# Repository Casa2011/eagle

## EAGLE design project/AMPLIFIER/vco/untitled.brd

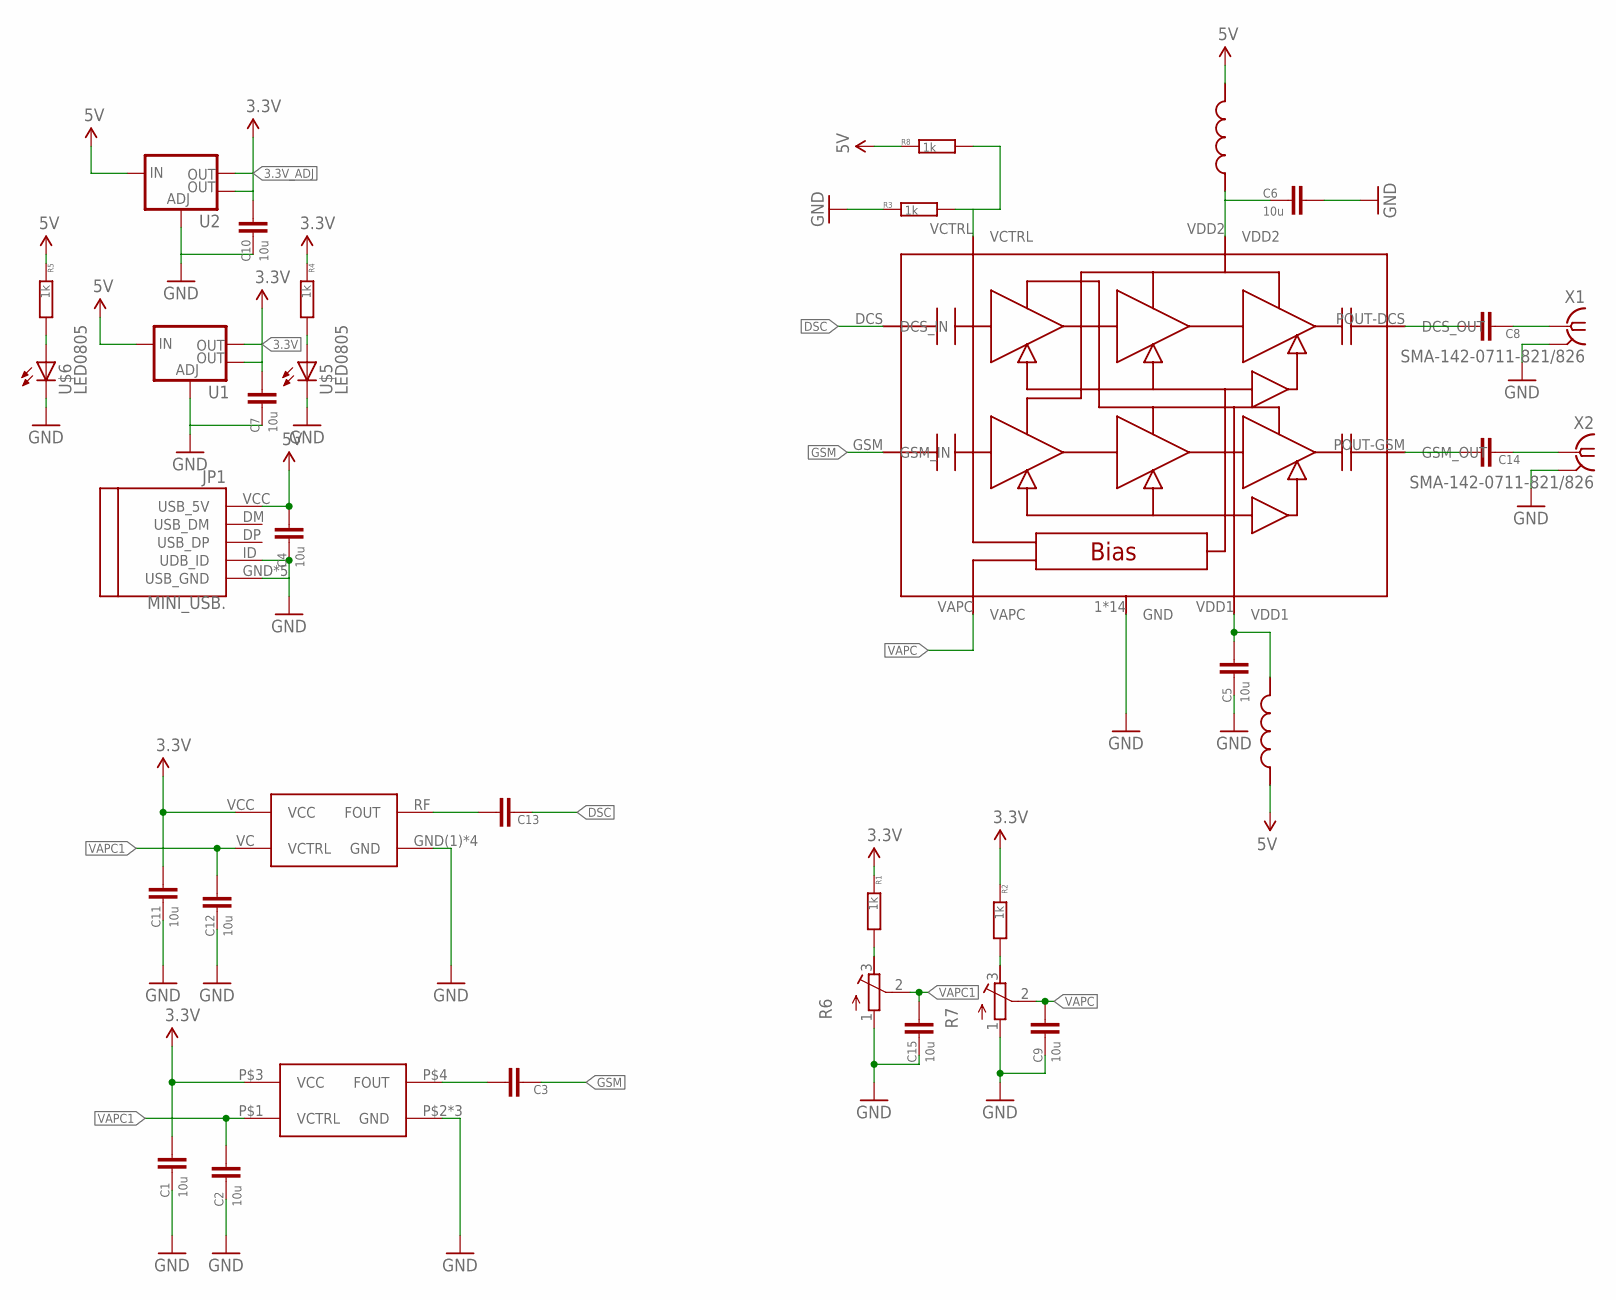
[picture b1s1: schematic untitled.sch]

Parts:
C1, C2, C4, C5, C6, C7, C9, C10, C11, C12, C15: 10u; C0805
C3, C8, C13, C14: CC0805; C0805
JP1: MINI_USB.; 32005-201
R1, R2, R3, R4, R5, R8: 1k; 0603
R6, R7: R-TRIMM64W; RTRIM64W
U1, U2: V_REG_LM1117SOT223; SOT223
U$1: FDK_IN089; FDK_IN_XX
U$2: RF-K-8A; RENESAS08123BA
U$3, U$4: L; L1
U$5, U$6: LED0805; 0805-LED
U$7: VCO_RX(1)
X1, X2: SMA-142-0711-821/826; J502-ND-142-0711-821/826

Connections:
3.3V: C1.1, C7.1, C11.1, R4.1, U1.2 (OUT), U1.4 (OUT), U$1.P$3 (VCC), U$7.VCC
3.3V_ADJ: C10.1, R1.1, R2.1, U2.2 (OUT), U2.4 (OUT)
5V: C4.1, JP1.VCC (USB_5V), R5.1, R8.1, U1.3 (IN), U2.3 (IN), U$3.2, U$4.1
DSC: C13.2, U$2.DCS (DCS_IN)
DSC->: C8.1, U$2.POUT-DCS (DCS_OUT)
GND: C1.2, C2.2, C4.2, C5.2, C6.1, C7.2, C9.2, C10.2, C11.2, C12.2, C15.2, JP1.GND (USB_GND), JP1.ID (UDB_ID), JP1.M1 (USB_GND), JP1.M2 (USB_GND), JP1.M3 (USB_GND), JP1.M4 (USB_GND), R3.1, R6.1 (A), R7.1 (A), U1.1 (ADJ), U2.1 (ADJ), U$1.P$2 (GND), U$1.P$5 (GND), U$1.P$6 (GND), U$2.1 (GND), U$2.2 (GND), U$2.3 (GND), U$2.4 (GND), U$2.5 (GND), U$2.6 (GND), U$2.7 (GND), U$2.8 (GND), U$2.9 (GND), U$2.10 (GND), U$2.11 (GND), U$2.12 (GND), U$2.13 (GND), U$2.14 (GND), U$5.C, U$6.C, U$7.GND(1) (GND), U$7.GND(2) (GND), U$7.GND(3) (GND), U$7.GND(4) (GND), X1.G@1 (2), X1.G@2 (2), X1.G@3 (2), X1.G@4 (2), X2.G@1 (2), X2.G@2 (2), X2.G@3 (2), X2.G@4 (2)
GSM: C3.2, U$2.GSM (GSM_IN)
unnamed: R1.2, R6.3 (E)
unnamed: R4.2, U$5.A
unnamed: R5.2, U$6.A
unnamed: R2.2, R7.3 (E)
unnamed: C3.1, U$1.P$4 (FOUT)
unnamed: C8.2, X1.1
unnamed: C6.2, U$2.VDD2, U$3.1
unnamed: C13.1, U$7.RF (FOUT)
unnamed: C14.2, X2.1
unnamed: C14.1, U$2.POUT-GSM (GSM_OUT)
unnamed: C5.1, U$2.VDD1, U$4.2
VAPC: C9.1, R7.2 (S), U$2.VAPC
VAPC1: C2.1, C12.1, C15.1, R6.2 (S), U$1.P$1 (VCTRL), U$7.VC (VCTRL)
VCTRL: R3.2, R8.2, U$2.VCTRL

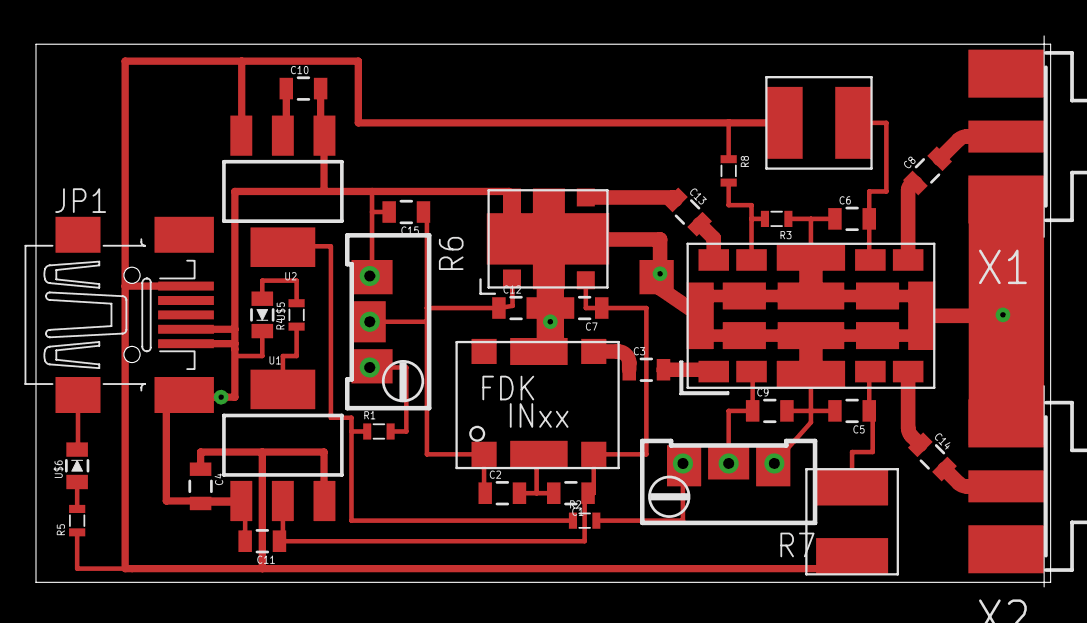
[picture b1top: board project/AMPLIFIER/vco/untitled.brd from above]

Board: 2 copper layers, 56.4 x 29.9 mm, 35 parts (0 on the bottom side), 21 nets.

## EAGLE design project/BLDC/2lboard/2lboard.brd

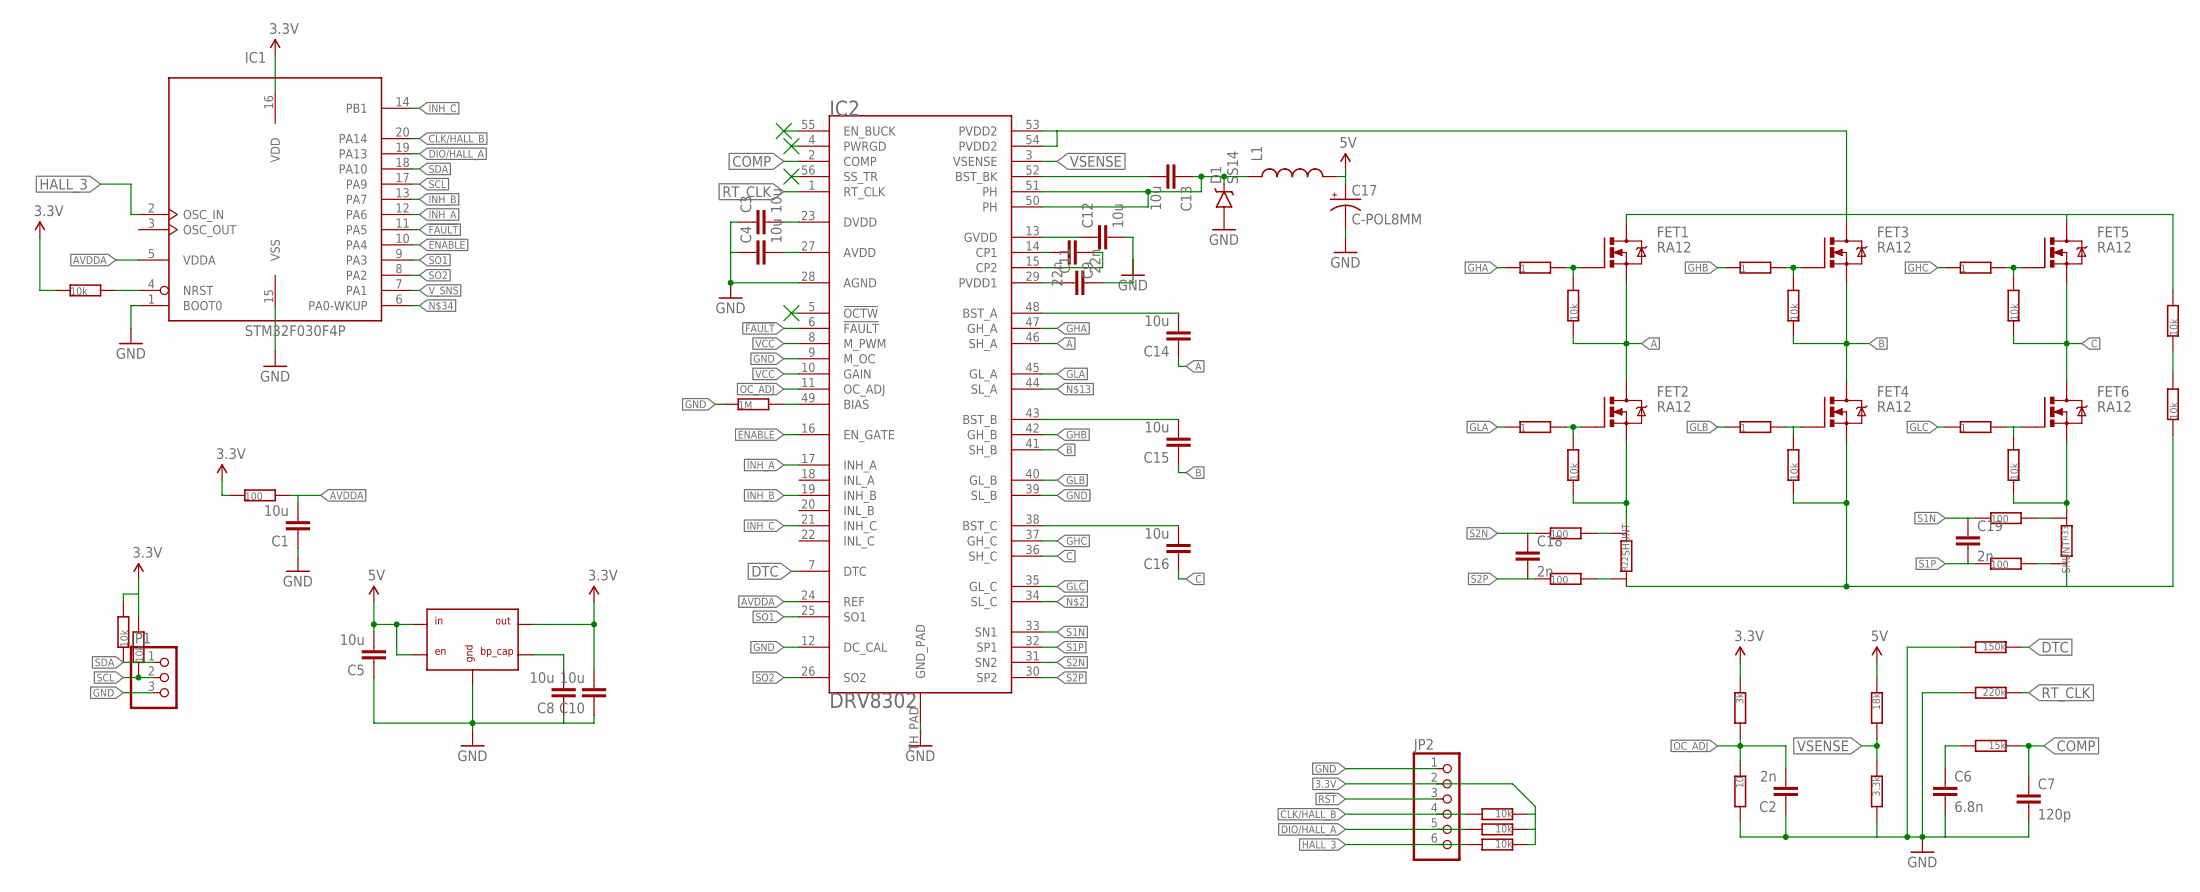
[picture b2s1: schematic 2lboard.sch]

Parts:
C1, C3, C4, C5, C8, C10, C12, C13, C14, C15, C16: 10u; C0805
C2, C18, C19: 2n; C0805
C6: 6.8n; C0805
C7: 120p; C0805
C9, C11: 22n; C0805
C17: C-POL8MM; PCAP8
D1: SS14; SMA-DIODE
FET1, FET2, FET3, FET4, FET5, FET6: RA12; POWERPAK_SO8
IC1: STM32F030F4P; TSSOP20-I
IC2: DRV8302; HTSSOP56DCA
IC3: LM258DG; SOT23-5L
JP1: PINHD-1X03_2.54; 1X03
JP2: PINHD-1X06_2.54; 1X06
L1: INDUCTORSRU1038; SRU1038
R1, R11, R12, R13, R14, R15, R20, R21, R25, R26, R31, R32, R34, R35: 10k; 0603
R2, R18, R19, R29, R30: 100; 0603
R3: 3k; 0603
R4: 10; 0603
R5: 1M; 0603
R6: 18k; 0603
R7: 3.3k; 0603
R8: 150k; 0603
R9: 220k; 0603
R10: 15k; 0603
R16, R17, R23, R24, R27, R28: 1; 0603
R22, R33: SHUNT

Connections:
3.3V: C10.2, IC1.16 (VDD), IC3.5 (OUT), JP2.2, R1.1, R2.1, R3.1, R11.2, R12.2, R13.1, R14.1, R15.1
5V: C5.2, C17.P$1 (+), IC3.1 (IN), IC3.3 (EN), L1.2, R6.1
!FAULT: IC1.11 (PA5), IC2.6 (!FAULT)
!RST: IC1.4 (NRST), JP2.3, R1.2
A: C14.1, FET1.1 (S), FET1.2 (S), FET1.3 (S), FET2.5 (D), FET2.6 (D), FET2.7 (D), FET2.8 (D), FET2.P$1 (D), IC2.46 (SH_A), R20.1
AVDDA: C1.2, IC1.5 (VDDA), IC2.24 (REF), R2.2
B: C15.1, FET3.1 (S), FET3.2 (S), FET3.3 (S), FET4.5 (D), FET4.6 (D), FET4.7 (D), FET4.8 (D), FET4.P$1 (D), IC2.41 (SH_B), R25.1
C: C16.1, FET5.1 (S), FET5.2 (S), FET5.3 (S), FET6.5 (D), FET6.6 (D), FET6.7 (D), FET6.8 (D), FET6.P$1 (D), IC2.36 (SH_C), R31.1
CLK/HALL_B: IC1.20 (PA14), JP2.4, R13.2
COMP: C7.1, IC2.2 (COMP), R10.1
DIO/HALL_A: IC1.19 (PA13), JP2.5, R14.2
DTC: IC2.7 (DTC), R8.1
ENABLE: IC1.10 (PA4), IC2.16 (EN_GATE)
GHA: IC2.47 (GH_A), R16.1
GHB: IC2.42 (GH_B), R23.1
GHC: IC2.37 (GH_C), R27.1
GLA: IC2.45 (GL_A), R17.1
GLB: IC2.40 (GL_B), R24.1
GLC: IC2.35 (GL_C), R28.1
GND: C1.1, C2.1, C3.1, C4.1, C5.1, C6.2, C7.2, C8.1, C10.1, C11.2, C12.2, C17.P$2 (-), D1.A, FET4.1 (S), FET4.2 (S), FET4.3 (S), IC1.1 (BOOT0), IC1.15 (VSS), IC2.9 (M_OC), IC2.12 (DC_CAL), IC2.28 (AGND), IC2.39 (SL_B), IC2.TH_PAD (GND_PAD), IC3.2 (GND), JP1.3, JP2.1, R4.2, R5.1, R7.2, R8.2, R9.2, R22.P$1 (1), R26.1, R33.P$2 (2), R35.1
HALL_3: IC1.2 (OSC_IN), JP2.6, R15.2
INH_A: IC1.12 (PA6), IC2.17 (INH_A)
INH_B: IC1.13 (PA7), IC2.19 (INH_B)
INH_C: IC1.14 (PB1), IC2.21 (INH_C)
unnamed: FET6.1 (S), FET6.2 (S), FET6.3 (S), IC2.34 (SL_C), R32.1, R33.P$1 (1)
unnamed: C14.2, IC2.48 (BST_A)
unnamed: C15.2, IC2.43 (BST_B)
unnamed: FET5.4 (G), R27.2, R31.2
unnamed: FET3.4 (G), R23.2, R25.2
unnamed: FET1.4 (G), R16.2, R20.2
unnamed: FET2.4 (G), R17.2, R21.2
unnamed: FET4.4 (G), R24.2, R26.2
unnamed: C16.2, IC2.38 (BST_C)
unnamed: FET6.4 (G), R28.2, R32.2
unnamed: IC2.49 (BIAS), R5.2
unnamed: FET2.1 (S), FET2.2 (S), FET2.3 (S), IC2.44 (SL_A), R21.1, R22.P$2 (2)
unnamed: C9.1, IC2.15 (CP2)
unnamed: C9.2, IC2.14 (CP1)
unnamed: C12.1, IC2.13 (GVDD)
unnamed: C13.2, IC2.52 (BST_BK)
unnamed: C13.1, D1.C, IC2.50 (PH), IC2.51 (PH), L1.1
unnamed: C6.1, R10.2
unnamed: C8.2, IC3.4 (CAP)
unnamed: C3.2, IC2.23 (DVDD)
unnamed: C4.2, IC2.27 (AVDD)
unnamed: C11.1, IC2.29 (PVDD1)
OC_ADJ: C2.2, IC2.11 (OC_ADJ), R3.2, R4.1
RT_CLK: IC2.1 (RT_CLK), R9.1
S1N: C19.1, IC2.33 (SN1), R29.1
S1P: C19.2, IC2.32 (SP1), R30.1
S2N: C18.1, IC2.31 (SN2), R18.1
S2P: C18.2, IC2.30 (SP2), R19.1
SCL: IC1.17 (PA9), JP1.2, R12.1
SDA: IC1.18 (PA10), JP1.1, R11.1
SO1: IC1.9 (PA3), IC2.25 (SO1)
SO2: IC1.8 (PA2), IC2.26 (SO2)
SS1N: R18.2, R22.P$4
SS1P: R19.2, R22.P$3
SS2N: R29.2, R33.P$3
SS2P: R30.2, R33.P$4
VCC: FET1.5 (D), FET1.6 (D), FET1.7 (D), FET1.8 (D), FET1.P$1 (D), FET3.5 (D), FET3.6 (D), FET3.7 (D), FET3.8 (D), FET3.P$1 (D), FET5.5 (D), FET5.6 (D), FET5.7 (D), FET5.8 (D), FET5.P$1 (D), IC2.8 (M_PWM), IC2.10 (GAIN), IC2.53 (PVDD2), IC2.54 (PVDD2), R34.2
VSENSE: IC2.3 (VSENSE), R6.2, R7.1
V_SNS: IC1.7 (PA1), R34.1, R35.2

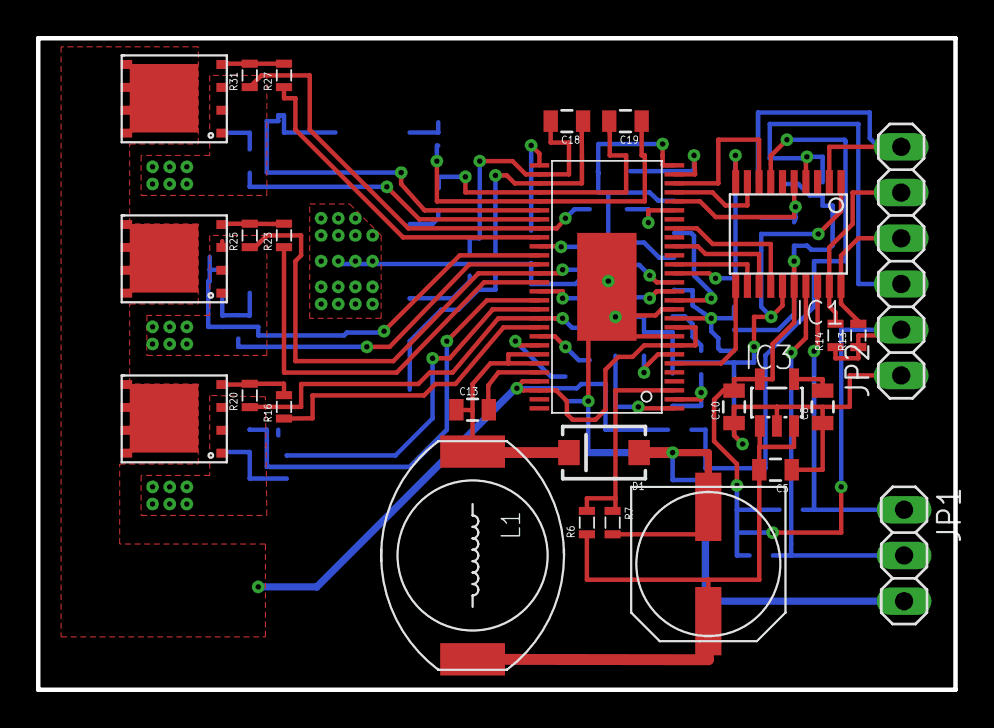
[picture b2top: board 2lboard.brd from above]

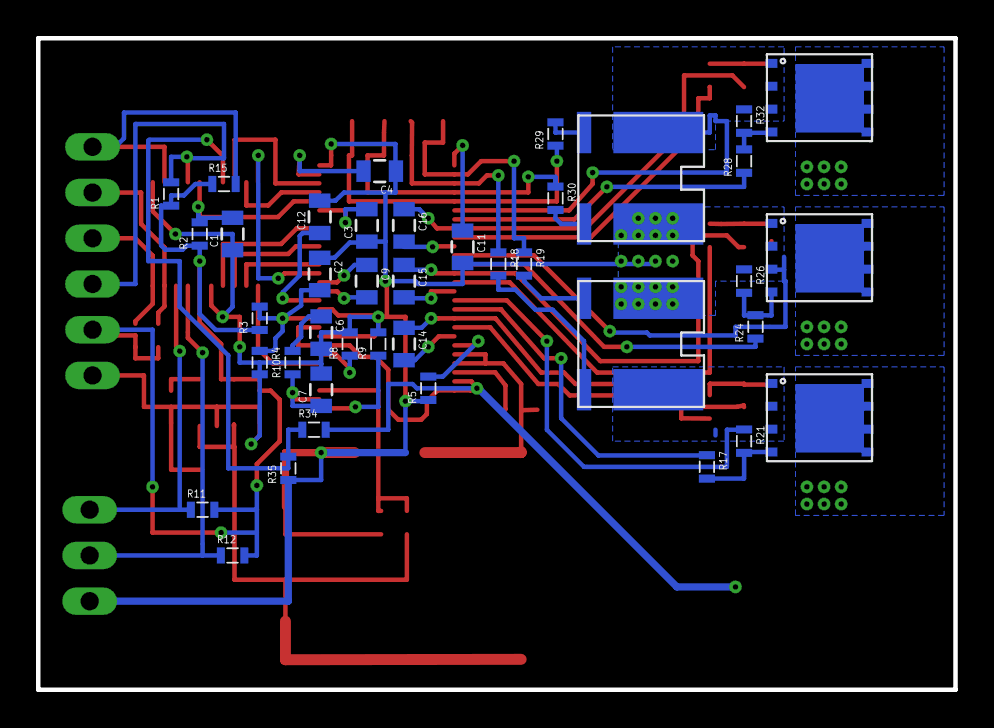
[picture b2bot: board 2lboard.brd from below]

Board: 2 copper layers, 51.0 x 36.2 mm, 67 parts (40 on the bottom side), 63 nets.

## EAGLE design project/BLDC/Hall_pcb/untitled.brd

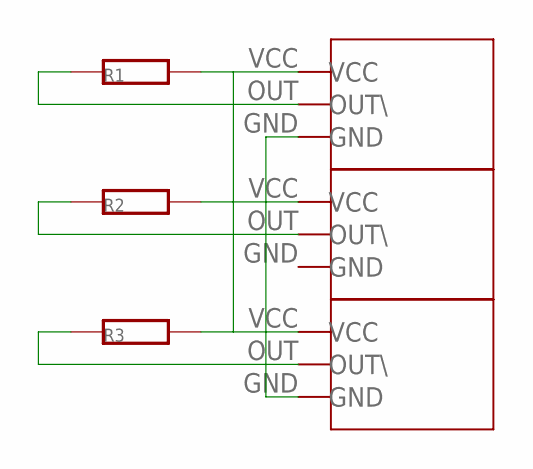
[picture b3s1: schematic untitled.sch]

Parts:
R1, R2, R3: R0603; 0603
U$1, U$2, U$3: HALL

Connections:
unnamed: U$1.GND, U$3.GND
unnamed: R1.2, R2.2, R3.2, U$1.VCC, U$2.VCC, U$3.VCC
unnamed: R1.1, U$1.OUT (OUT\)
unnamed: R2.1, U$2.OUT (OUT\)
unnamed: R3.1, U$3.OUT (OUT\)

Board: 2 copper layers, 6 parts (0 on the bottom side), 5 nets, no tracks yet.

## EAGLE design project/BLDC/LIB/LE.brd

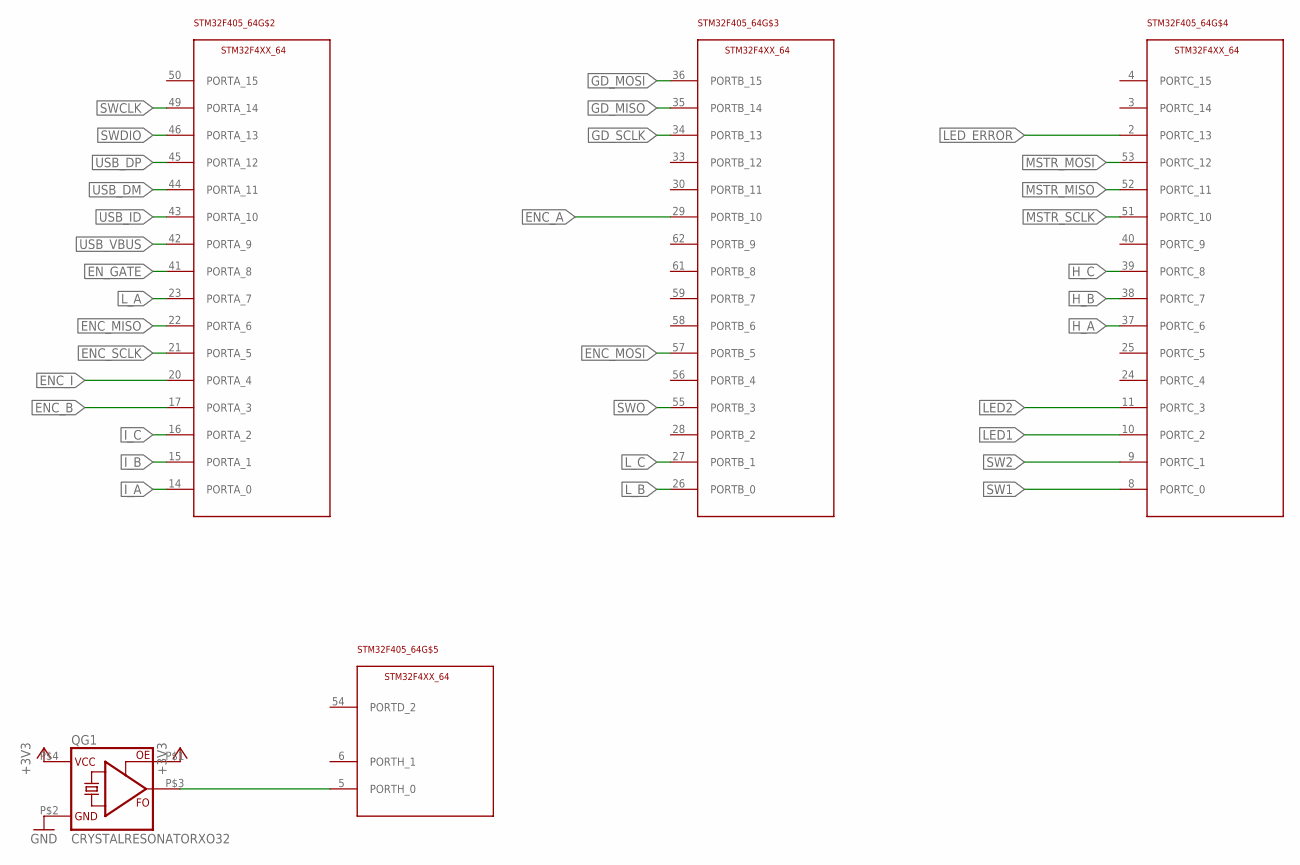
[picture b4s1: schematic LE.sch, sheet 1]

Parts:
QG1: CRYSTALRESONATORXO32; XO32
STM32F405_64: STM32F4XX_64; TQFP64

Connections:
+3V3: QG1.P$1 (OE), QG1.P$4 (VCC); also elsewhere on the board
ENC_A: STM32F405_64.29 (PORTB_10); also elsewhere on the board
ENC_B: STM32F405_64.17 (PORTA_3); also elsewhere on the board
ENC_I: STM32F405_64.20 (PORTA_4); also elsewhere on the board
ENC_MISO: STM32F405_64.22 (PORTA_6); also elsewhere on the board
ENC_MOSI: STM32F405_64.57 (PORTB_5); also elsewhere on the board
ENC_SCLK: STM32F405_64.21 (PORTA_5); also elsewhere on the board
EN_GATE: STM32F405_64.41 (PORTA_8); also elsewhere on the board
GD_MISO: STM32F405_64.35 (PORTB_14); also elsewhere on the board
GD_MOSI: STM32F405_64.36 (PORTB_15); also elsewhere on the board
GD_SCLK: STM32F405_64.34 (PORTB_13); also elsewhere on the board
GND: QG1.P$2 (GND); also elsewhere on the board
H_A: STM32F405_64.37 (PORTC_6); also elsewhere on the board
H_B: STM32F405_64.38 (PORTC_7); also elsewhere on the board
H_C: STM32F405_64.39 (PORTC_8); also elsewhere on the board
I_A: STM32F405_64.14 (PORTA_0); also elsewhere on the board
I_B: STM32F405_64.15 (PORTA_1); also elsewhere on the board
I_C: STM32F405_64.16 (PORTA_2); also elsewhere on the board
LED1: STM32F405_64.10 (PORTC_2); also elsewhere on the board
LED2: STM32F405_64.11 (PORTC_3); also elsewhere on the board
LED_ERROR: STM32F405_64.2 (PORTC_13); also elsewhere on the board
L_A: STM32F405_64.23 (PORTA_7); also elsewhere on the board
L_B: STM32F405_64.26 (PORTB_0); also elsewhere on the board
L_C: STM32F405_64.27 (PORTB_1); also elsewhere on the board
MSTR_MISO: STM32F405_64.52 (PORTC_11); also elsewhere on the board
MSTR_MOSI: STM32F405_64.53 (PORTC_12); also elsewhere on the board
MSTR_SCLK: STM32F405_64.51 (PORTC_10); also elsewhere on the board
unnamed: QG1.P$3 (FO), STM32F405_64.5 (PORTH_0)
SW1: STM32F405_64.8 (PORTC_0); also elsewhere on the board
SW2: STM32F405_64.9 (PORTC_1); also elsewhere on the board
SWCLK: STM32F405_64.49 (PORTA_14); also elsewhere on the board
SWDIO: STM32F405_64.46 (PORTA_13); also elsewhere on the board
SWO: STM32F405_64.55 (PORTB_3); also elsewhere on the board
USB_DM: STM32F405_64.44 (PORTA_11); also elsewhere on the board
USB_DP: STM32F405_64.45 (PORTA_12); also elsewhere on the board
USB_ID: STM32F405_64.43 (PORTA_10); also elsewhere on the board
USB_VBUS: STM32F405_64.42 (PORTA_9); also elsewhere on the board

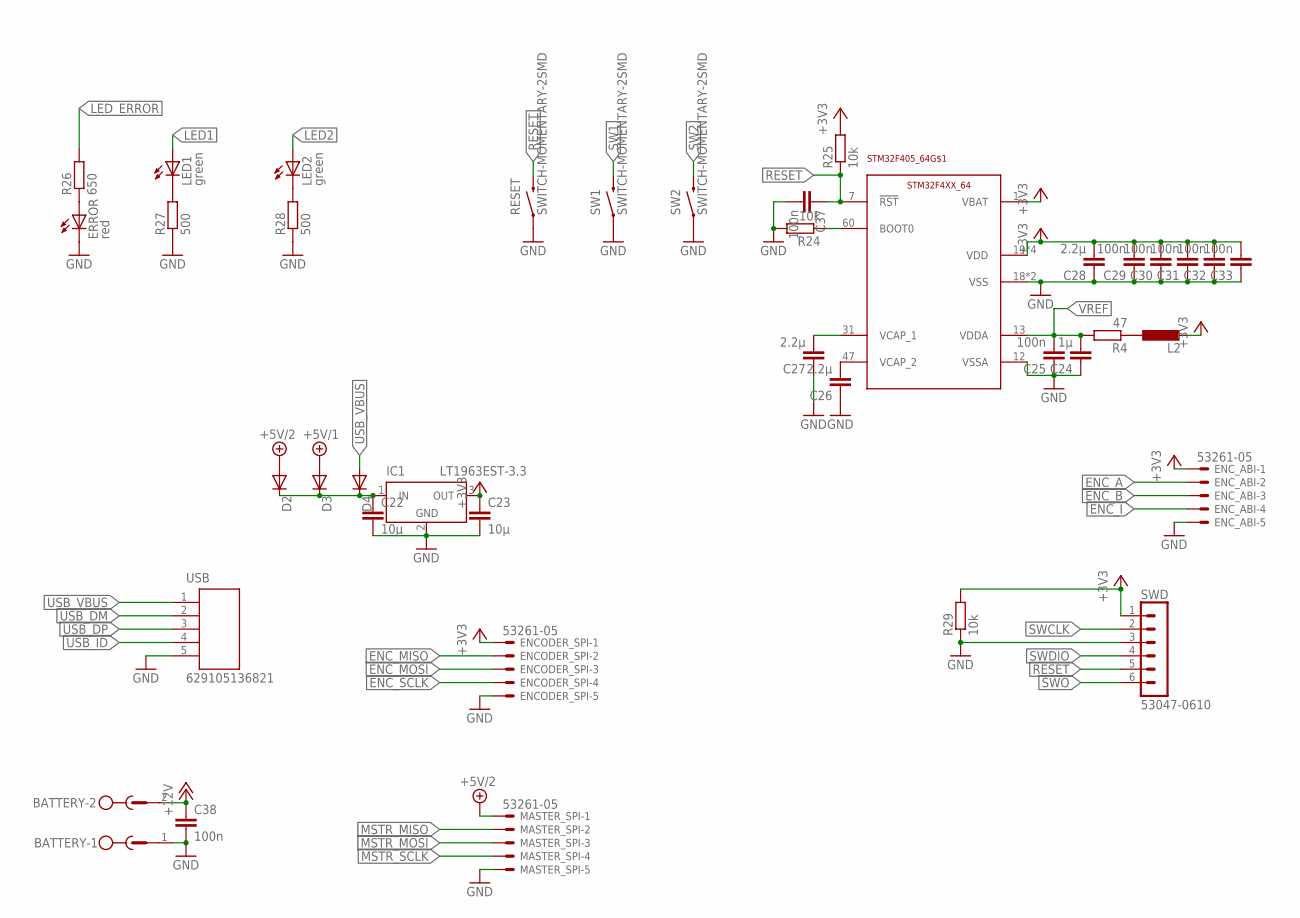
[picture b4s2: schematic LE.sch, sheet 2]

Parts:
BATTERY: MSTBV2
C22, C23: 10µ; C0805
C24: 1µ; C0805
C25, C29, C30, C31, C32, C33, C37, C38: 100n; C0805
C26, C27, C28: 2.2µ; C0805
D2, D3, D4: DIODE-DO214AC; DO214AC
ENCODER_SPI: 53261-05
ENC_ABI: 53261-05
ERROR: red; CHIP-LED0805
IC1: LT1963EST-3.3; SOT223
L2: L-EUL2012C; L2012C
LED1, LED2: green; CHIP-LED0805
MASTER_SPI: 53261-05
R4: 47; R0805
R24, R25, R29: 10k; R0805
R26: 650; R0805
R27, R28: 500; R0805
RESET: SWITCH-MOMENTARY-2SMD; TACTILE-SWITCH-SMD
STM32F405_64: STM32F4XX_64; TQFP64
SW1, SW2: SWITCH-MOMENTARY-2SMD; TACTILE-SWITCH-SMD
SWD: 53047-0610
USB: 629105136821

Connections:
+3V3: C23.1, C28.2, C29.2, C30.2, C31.2, C32.2, C33.2, ENCODER_SPI.1, ENC_ABI.1, IC1.3 (OUT), L2.2, R25.2, R29.2, STM32F405_64.1 (VBAT), STM32F405_64.19 (VDD), STM32F405_64.32 (VDD), STM32F405_64.48 (VDD), STM32F405_64.64 (VDD), SWD.1; also elsewhere on the board
+5V/1: D3.A; also elsewhere on the board
+5V/2: D2.A, MASTER_SPI.1
+12V: BATTERY.2, C38.1; also elsewhere on the board
ENC_A: ENC_ABI.2; also elsewhere on the board
ENC_B: ENC_ABI.3; also elsewhere on the board
ENC_I: ENC_ABI.4; also elsewhere on the board
ENC_MISO: ENCODER_SPI.2; also elsewhere on the board
ENC_MOSI: ENCODER_SPI.3; also elsewhere on the board
ENC_SCLK: ENCODER_SPI.4; also elsewhere on the board
GND: BATTERY.1, C22.2, C23.2, C24.1, C25.1, C26.1, C27.1, C28.1, C29.1, C30.1, C31.1, C32.1, C33.1, C37.2, C38.2, ENCODER_SPI.5, ENC_ABI.5, ERROR.C, IC1.2 (GND), IC1.4 (GND), MASTER_SPI.5, R24.2, R27.1, R28.1, R29.1, RESET.1, STM32F405_64.12 (VSSA), STM32F405_64.18 (VSS), STM32F405_64.63 (VSS), SW1.1, SW2.1, SWD.3, USB.5; also elsewhere on the board
LED1: LED1.A; also elsewhere on the board
LED2: LED2.A; also elsewhere on the board
LED_ERROR: R26.2; also elsewhere on the board
MSTR_MISO: MASTER_SPI.2; also elsewhere on the board
MSTR_MOSI: MASTER_SPI.3; also elsewhere on the board
MSTR_SCLK: MASTER_SPI.4; also elsewhere on the board
unnamed: L2.1, R4.1
unnamed: C26.2, STM32F405_64.47 (VCAP_2)
unnamed: C27.2, STM32F405_64.31 (VCAP_1)
unnamed: LED1.C, R27.2
unnamed: C22.1, D2.C, D3.C, D4.C, IC1.1 (IN)
unnamed: LED2.C, R28.2
unnamed: R24.1, STM32F405_64.60 (BOOT0)
unnamed: ERROR.A, R26.1
RESET: C37.1, R25.1, RESET.3 (2), STM32F405_64.7 (!RST), SWD.5
SW1: SW1.3 (2); also elsewhere on the board
SW2: SW2.3 (2); also elsewhere on the board
SWCLK: SWD.2; also elsewhere on the board
SWDIO: SWD.4; also elsewhere on the board
SWO: SWD.6; also elsewhere on the board
USB_DM: USB.2; also elsewhere on the board
USB_DP: USB.3; also elsewhere on the board
USB_ID: USB.4; also elsewhere on the board
USB_VBUS: D4.A, USB.1; also elsewhere on the board
VREF: C24.2, C25.2, R4.2, STM32F405_64.13 (VDDA); also elsewhere on the board

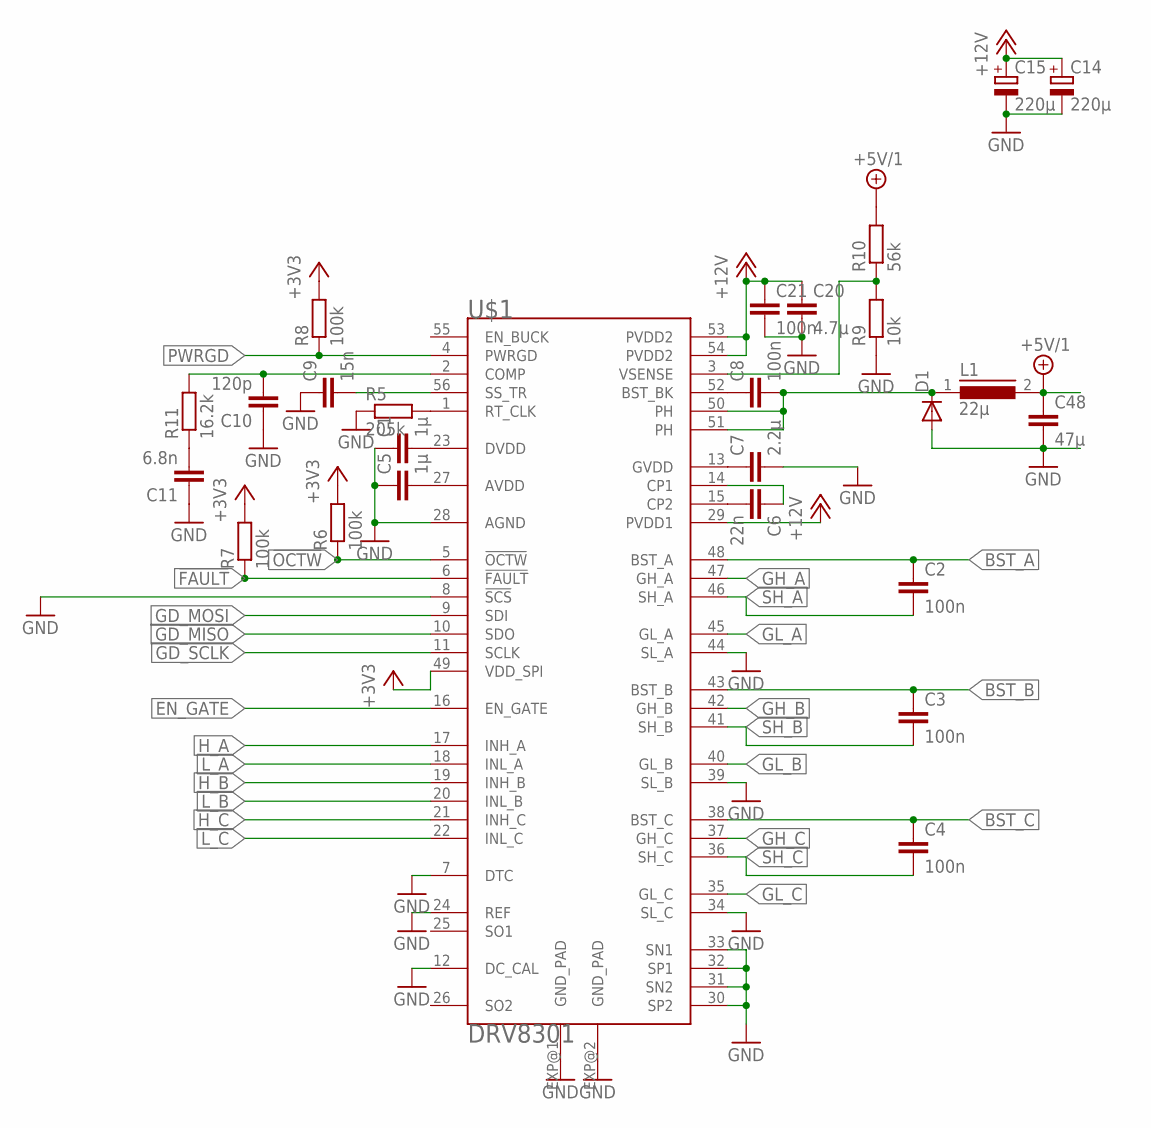
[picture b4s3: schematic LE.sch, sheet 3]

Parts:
C1, C5: 1µ; C0805
C2, C3, C4, C8, C21: 100n; C0805
C6: 22n; C0805
C7: 2.2µ; C0805
C9: 15n; C0805
C10: 120p; C0805
C11: 6.8n; C0805
C14, C15: 220µ; PANASONIC_G
C20: 4.7µ; C0805
C48: 47µ; C1206
D1: DIODE-DO-214AC; DO-214AC
L1: 22µ; DR127
R5: 205k; R0805
R6, R7, R8: 100k; R0805
R9: 10k; R0805
R10: 56k; R0805
R11: 16.2k; R0805
U$1: DRV8301; HTSSOP56DCA

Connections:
!FAULT: R7.1, U$1.6 (!FAULT)
!OCTW: R6.1, U$1.5 (!OCTW)
+3V3: R6.2, R7.2, R8.2, U$1.49 (VDD_SPI); also elsewhere on the board
+5V/1: C48.1, L1.2, R10.2; also elsewhere on the board
+12V: C14.+, C15.+, C20.1, C21.1, U$1.29 (PVDD1), U$1.53 (PVDD2), U$1.54 (PVDD2); also elsewhere on the board
BST_A: C2.1, U$1.48 (BST_A); also elsewhere on the board
BST_B: C3.1, U$1.43 (BST_B); also elsewhere on the board
BST_C: C4.1, U$1.38 (BST_C); also elsewhere on the board
EN_GATE: U$1.16 (EN_GATE); also elsewhere on the board
GD_MISO: U$1.10 (SDO); also elsewhere on the board
GD_MOSI: U$1.9 (SDI); also elsewhere on the board
GD_SCLK: U$1.11 (SCLK); also elsewhere on the board
GH_A: U$1.47 (GH_A); also elsewhere on the board
GH_B: U$1.42 (GH_B); also elsewhere on the board
GH_C: U$1.37 (GH_C); also elsewhere on the board
GL_A: U$1.45 (GL_A); also elsewhere on the board
GL_B: U$1.40 (GL_B); also elsewhere on the board
GL_C: U$1.35 (GL_C); also elsewhere on the board
GND: C1.1, C5.1, C7.2, C9.1, C10.1, C11.1, C14.-, C15.-, C20.2, C21.2, C48.2, D1.A, R5.1, R9.1, U$1.7 (DTC), U$1.8 (!SCS), U$1.12 (DC_CAL), U$1.24 (REF), U$1.28 (AGND), U$1.30 (SP2), U$1.31 (SN2), U$1.32 (SP1), U$1.33 (SN1), U$1.34 (SL_C), U$1.39 (SL_B), U$1.44 (SL_A), U$1.EXP@1 (GND_PAD), U$1.EXP@2 (GND_PAD); also elsewhere on the board
H_A: U$1.17 (INH_A); also elsewhere on the board
H_B: U$1.19 (INH_B); also elsewhere on the board
H_C: U$1.21 (INH_C); also elsewhere on the board
L_A: U$1.18 (INL_A); also elsewhere on the board
L_B: U$1.20 (INL_B); also elsewhere on the board
L_C: U$1.22 (INL_C); also elsewhere on the board
unnamed: R5.2, U$1.1 (RT_CLK)
unnamed: C1.2, U$1.23 (DVDD)
unnamed: C5.2, U$1.27 (AVDD)
unnamed: C6.1, U$1.14 (CP1)
unnamed: C6.2, U$1.15 (CP2)
unnamed: C7.1, U$1.13 (GVDD)
unnamed: C8.1, U$1.52 (BST_BK)
unnamed: C8.2, D1.C, L1.1, U$1.50 (PH), U$1.51 (PH)
unnamed: C9.2, U$1.56 (SS_TR)
unnamed: R9.2, R10.1, U$1.3 (VSENSE)
unnamed: C11.2, R11.1
unnamed: C10.2, R11.2, U$1.2 (COMP)
PWRGD: R8.1, U$1.4 (PWRGD)
SH_A: C2.2, U$1.46 (SH_A); also elsewhere on the board
SH_B: C3.2, U$1.41 (SH_B); also elsewhere on the board
SH_C: C4.2, U$1.36 (SH_C); also elsewhere on the board

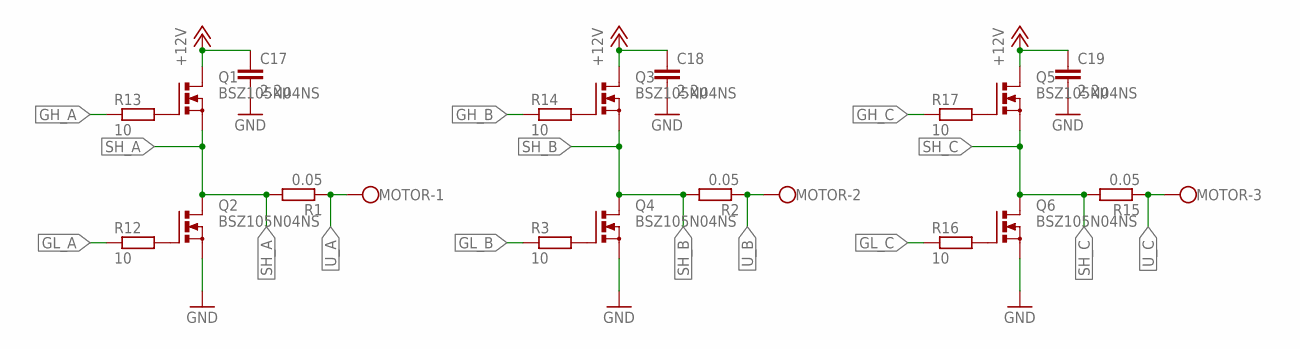
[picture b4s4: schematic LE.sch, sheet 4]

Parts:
C17, C18, C19: 2.2µ; C0805
MOTOR: W237-103
Q1, Q2, Q3, Q4, Q5, Q6: BSZ105N04NS; PG-TDSON-8
R1, R2, R15: 0.05; R1206
R3, R12, R16: 10; R1206
R13, R14, R17: 10; R0805

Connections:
+12V: C17.1, C18.1, C19.1, Q1.5 (D), Q1.6 (D), Q1.7 (D), Q1.8 (D), Q1.TH (D), Q3.5 (D), Q3.6 (D), Q3.7 (D), Q3.8 (D), Q3.TH (D), Q5.5 (D), Q5.6 (D), Q5.7 (D), Q5.8 (D), Q5.TH (D); also elsewhere on the board
GH_A: R13.1; also elsewhere on the board
GH_B: R14.1; also elsewhere on the board
GH_C: R17.1; also elsewhere on the board
GL_A: R12.1; also elsewhere on the board
GL_B: R3.1; also elsewhere on the board
GL_C: R16.1; also elsewhere on the board
GND: C17.2, C18.2, C19.2, Q2.1 (S), Q2.2 (S), Q2.3 (S), Q4.1 (S), Q4.2 (S), Q4.3 (S), Q6.1 (S), Q6.2 (S), Q6.3 (S); also elsewhere on the board
unnamed: Q3.4 (G), R14.2
unnamed: Q1.4 (G), R13.2
unnamed: Q4.4 (G), R3.2
unnamed: Q5.4 (G), R17.2
unnamed: Q6.4 (G), R16.2
unnamed: Q2.4 (G), R12.2
SH_A: Q1.1 (S), Q1.2 (S), Q1.3 (S), Q2.5 (D), Q2.6 (D), Q2.7 (D), Q2.8 (D), Q2.TH (D), R1.2; also elsewhere on the board
SH_B: Q3.1 (S), Q3.2 (S), Q3.3 (S), Q4.5 (D), Q4.6 (D), Q4.7 (D), Q4.8 (D), Q4.TH (D), R2.2; also elsewhere on the board
SH_C: Q5.1 (S), Q5.2 (S), Q5.3 (S), Q6.5 (D), Q6.6 (D), Q6.7 (D), Q6.8 (D), Q6.TH (D), R15.2; also elsewhere on the board
U_A: MOTOR.1, R1.1; also elsewhere on the board
U_B: MOTOR.2, R2.1; also elsewhere on the board
U_C: MOTOR.3, R15.1; also elsewhere on the board

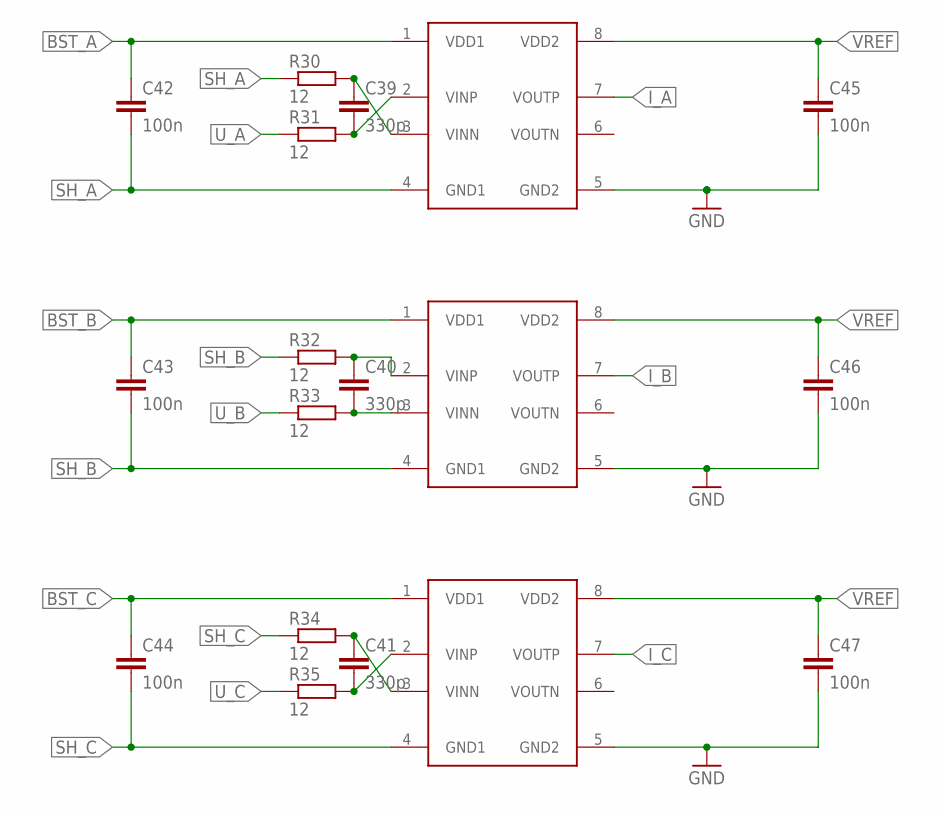
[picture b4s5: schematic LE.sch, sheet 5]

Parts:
C39, C40, C41: 330p; C0805
C42, C43, C44, C45, C46, C47: 100n; C1206
R30, R31, R32, R33, R34, R35: 12; R0805
U$2, U$3, U$4: AMC1200; SOIC8

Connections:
BST_A: C42.1, U$2.1 (VDD1); also elsewhere on the board
BST_B: C43.1, U$3.1 (VDD1); also elsewhere on the board
BST_C: C44.1, U$4.1 (VDD1); also elsewhere on the board
GND: C45.2, C46.2, C47.2, U$2.5 (GND2), U$3.5 (GND2), U$4.5 (GND2); also elsewhere on the board
I_A: U$2.7 (VOUTP); also elsewhere on the board
I_B: U$3.7 (VOUTP); also elsewhere on the board
I_C: U$4.7 (VOUTP); also elsewhere on the board
unnamed: C39.1, R30.2, U$2.3 (VINN)
unnamed: C39.2, R31.2, U$2.2 (VINP)
unnamed: C40.2, R33.2, U$3.3 (VINN)
unnamed: C40.1, R32.2, U$3.2 (VINP)
unnamed: C41.1, R34.2, U$4.3 (VINN)
unnamed: C41.2, R35.2, U$4.2 (VINP)
SH_A: C42.2, R30.1, U$2.4 (GND1); also elsewhere on the board
SH_B: C43.2, R32.1, U$3.4 (GND1); also elsewhere on the board
SH_C: C44.2, R34.1, U$4.4 (GND1); also elsewhere on the board
U_A: R31.1; also elsewhere on the board
U_B: R33.1; also elsewhere on the board
U_C: R35.1; also elsewhere on the board
VREF: C45.1, C46.1, C47.1, U$2.8 (VDD2), U$3.8 (VDD2), U$4.8 (VDD2); also elsewhere on the board

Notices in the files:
parts and their libraries:
SparkFun-Aesthetics: Licensing: Creative Commons ShareAlike 4.0 International - https://creativecommons.org/licenses/by-sa/4.0
USBSteckverbinderWR-COM: Copyright: Würth Elektronik
con-molex-picoblade: Copyright (C) 2010, Bob Starr
